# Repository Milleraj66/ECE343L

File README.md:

# ECE343L
MC68000 Eagle Schematic and Board

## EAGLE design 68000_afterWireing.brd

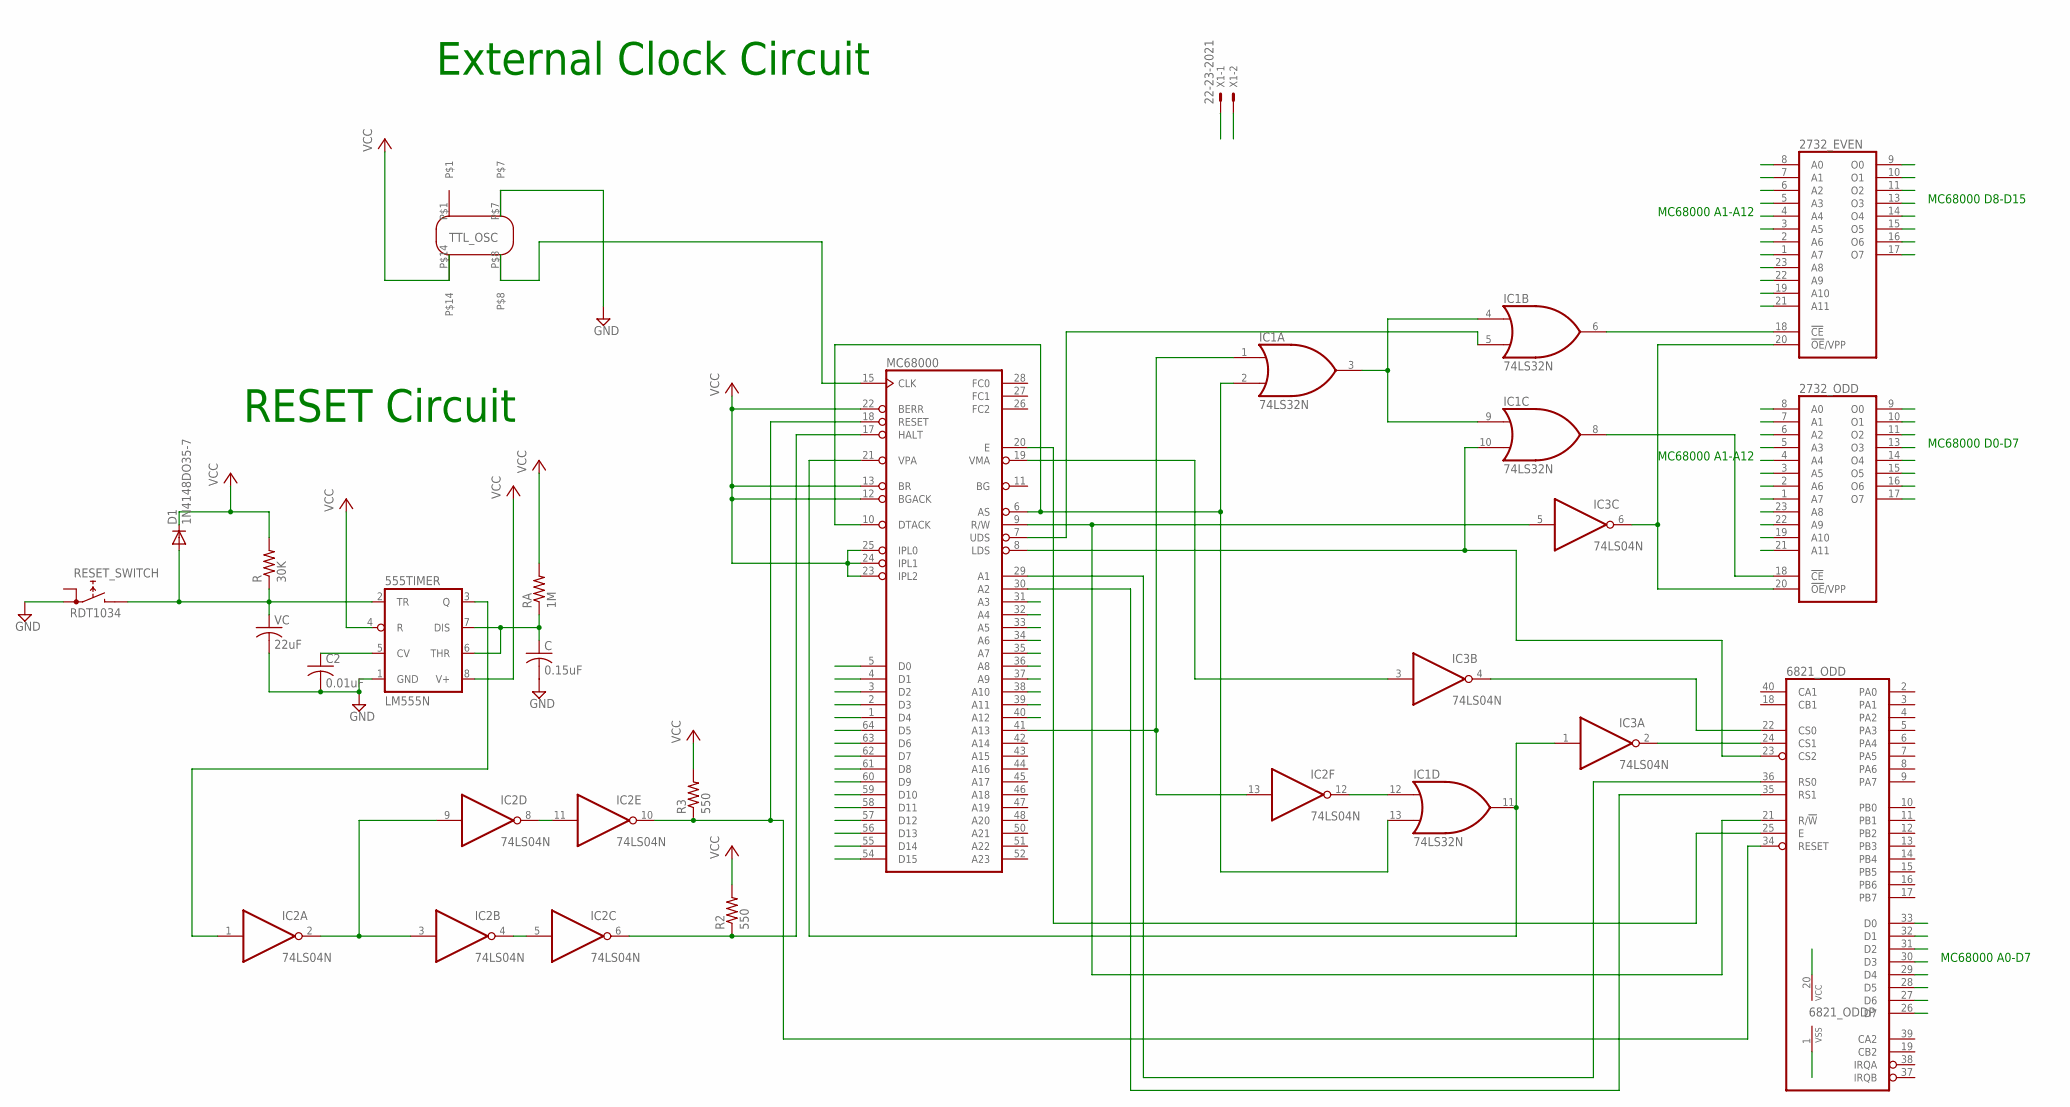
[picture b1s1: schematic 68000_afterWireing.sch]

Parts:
555TIMER: LM555N; DIL08
2732_EVEN, 2732_ODD: 2732; DIL24
6821_ODD: 6821; DIL40
C: 0.15uF; C025-024X044
C2: 0.01uF; C025-024X044
D1: 1N4148DO35-7; DO35-7
IC1: 74LS32N; DIL14
IC2, IC3: 74LS04N; DIL14
MC68000: MC68000P; DIL64
R: 30K; 0204V
R2, R3: 550; 0204V
RA: 1M; 0204V
RESET_SWITCH: RDT1034
U$1: TTL_OSCILLATOR
VC: 22uF; C025-024X044
X1: 22-23-2021

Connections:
A1: 2732_EVEN.8 (A0), 2732_ODD.8 (A0), 6821_ODD.36 (RS0), MC68000.29 (A1)
A2: 2732_EVEN.7 (A1), 2732_ODD.7 (A1), 6821_ODD.35 (RS1), MC68000.30 (A2)
A3: 2732_EVEN.6 (A2), 2732_ODD.6 (A2), MC68000.31 (A3)
A4: 2732_EVEN.5 (A3), 2732_ODD.5 (A3), MC68000.32 (A4)
A5: 2732_EVEN.4 (A4), 2732_ODD.4 (A4), MC68000.33 (A5)
A6: 2732_EVEN.3 (A5), 2732_ODD.3 (A5), MC68000.34 (A6)
A7: 2732_EVEN.2 (A6), 2732_ODD.2 (A6), MC68000.35 (A7)
A8: 2732_EVEN.1 (A7), 2732_ODD.1 (A7), MC68000.36 (A8)
A9: 2732_EVEN.23 (A8), 2732_ODD.23 (A8), MC68000.37 (A9)
A10: 2732_EVEN.22 (A9), 2732_ODD.22 (A9), MC68000.38 (A10)
A11: 2732_EVEN.19 (A10), 2732_ODD.19 (A10), MC68000.39 (A11)
A12: 2732_EVEN.21 (A11), 2732_ODD.21 (A11), MC68000.40 (A12)
D0: 2732_ODD.9 (O0), 6821_ODD.33 (D0), MC68000.5 (D0)
D1: 2732_ODD.10 (O1), 6821_ODD.32 (D1), MC68000.4 (D1)
D2: 2732_ODD.11 (O2), 6821_ODD.31 (D2), MC68000.3 (D2)
D3: 2732_ODD.13 (O3), 6821_ODD.30 (D3), MC68000.2 (D3)
D4: 2732_ODD.14 (O4), 6821_ODD.29 (D4), MC68000.1 (D4)
D5: 2732_ODD.15 (O5), 6821_ODD.28 (D5), MC68000.64 (D5)
D6: 2732_ODD.16 (O6), 6821_ODD.27 (D6), MC68000.63 (D6)
D7: 2732_ODD.17 (O7), 6821_ODD.26 (D7), MC68000.62 (D7)
D8: 2732_EVEN.9 (O0), MC68000.61 (D8)
D9: 2732_EVEN.10 (O1), MC68000.60 (D9)
D10: 2732_EVEN.11 (O2), MC68000.59 (D10)
D11: 2732_EVEN.13 (O3), MC68000.58 (D11)
D12: 2732_EVEN.14 (O4), MC68000.57 (D12)
D13: 2732_EVEN.15 (O5), MC68000.56 (D13)
D14: 2732_EVEN.16 (O6), MC68000.55 (D14)
D15: 2732_EVEN.17 (O7), MC68000.54 (D15)
GND: 555TIMER.1 (GND), 2732_EVEN.12 (GND), 2732_ODD.12 (GND), 6821_ODD.1 (VSS), C.2, C2.2, IC1.7 (GND), IC2.7 (GND), IC3.7 (GND), MC68000.16 (GND), MC68000.53 (GND), RESET_SWITCH.A1, U$1.P$7, VC.2, X1.2
unnamed: 6821_ODD.21 (R/!W), IC3.5 (I), MC68000.9 (R/W)
unnamed: 6821_ODD.24 (CS1), IC3.2 (O)
unnamed: IC1.1 (I0), IC2.13 (I), MC68000.41 (A13)
unnamed: IC1.3 (O), IC1.4 (I0), IC1.9 (I0)
unnamed: 2732_EVEN.20 (!OE!/VPP), 2732_ODD.20 (!OE!/VPP), IC3.6 (O)
unnamed: 6821_ODD.25 (E), MC68000.20 (E)
unnamed: IC1.5 (I1), MC68000.7 (UDS)
unnamed: 6821_ODD.23 (CS2), IC1.10 (I1), MC68000.8 (LDS)
unnamed: IC1.2 (I1), IC1.13 (I1), MC68000.6 (AS), MC68000.10 (DTACK)
unnamed: 6821_ODD.22 (CS0), IC3.4 (O)
unnamed: IC3.3 (I), MC68000.19 (VMA)
unnamed: IC1.12 (I0), IC2.12 (O)
unnamed: IC1.11 (O), IC3.1 (I), MC68000.21 (VPA)
unnamed: 555TIMER.5 (CV), C2.1
unnamed: 555TIMER.2 (TR), D1.A, R.1, RESET_SWITCH.B, VC.1
unnamed: 2732_EVEN.18 (!CE), IC1.6 (O)
unnamed: 555TIMER.6 (THR), 555TIMER.7 (DIS), C.1, RA.1
unnamed: 555TIMER.3 (Q), IC2.1 (I)
unnamed: IC2.4 (O), IC2.5 (I)
unnamed: IC2.6 (O), MC68000.17 (HALT), R2.1
unnamed: 6821_ODD.34 (RESET), IC2.10 (O), MC68000.18 (RESET), R3.1
unnamed: 2732_ODD.18 (!CE), IC1.8 (O)
unnamed: MC68000.15 (CLK), U$1.P$8
unnamed: IC2.2 (O), IC2.3 (I), IC2.9 (I)
unnamed: IC2.8 (O), IC2.11 (I)
VCC: 555TIMER.4 (R), 555TIMER.8 (V+), 2732_EVEN.24 (VCC), 2732_ODD.24 (VCC), 6821_ODD.20 (VCC), D1.C, IC1.14 (VCC), IC2.14 (VCC), IC3.14 (VCC), MC68000.12 (BGACK), MC68000.13 (BR), MC68000.14 (VCC), MC68000.22 (BERR), MC68000.23 (IPL2), MC68000.24 (IPL1), MC68000.25 (IPL0), MC68000.49 (VCC), R.2, R2.2, R3.2, RA.2, U$1.P$14, X1.1

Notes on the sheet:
RESET Circuit
External Clock Circuit
MC68000 D8-D15
MC68000 D0-D7
MC68000 A1-A12
MC68000 A0-D7

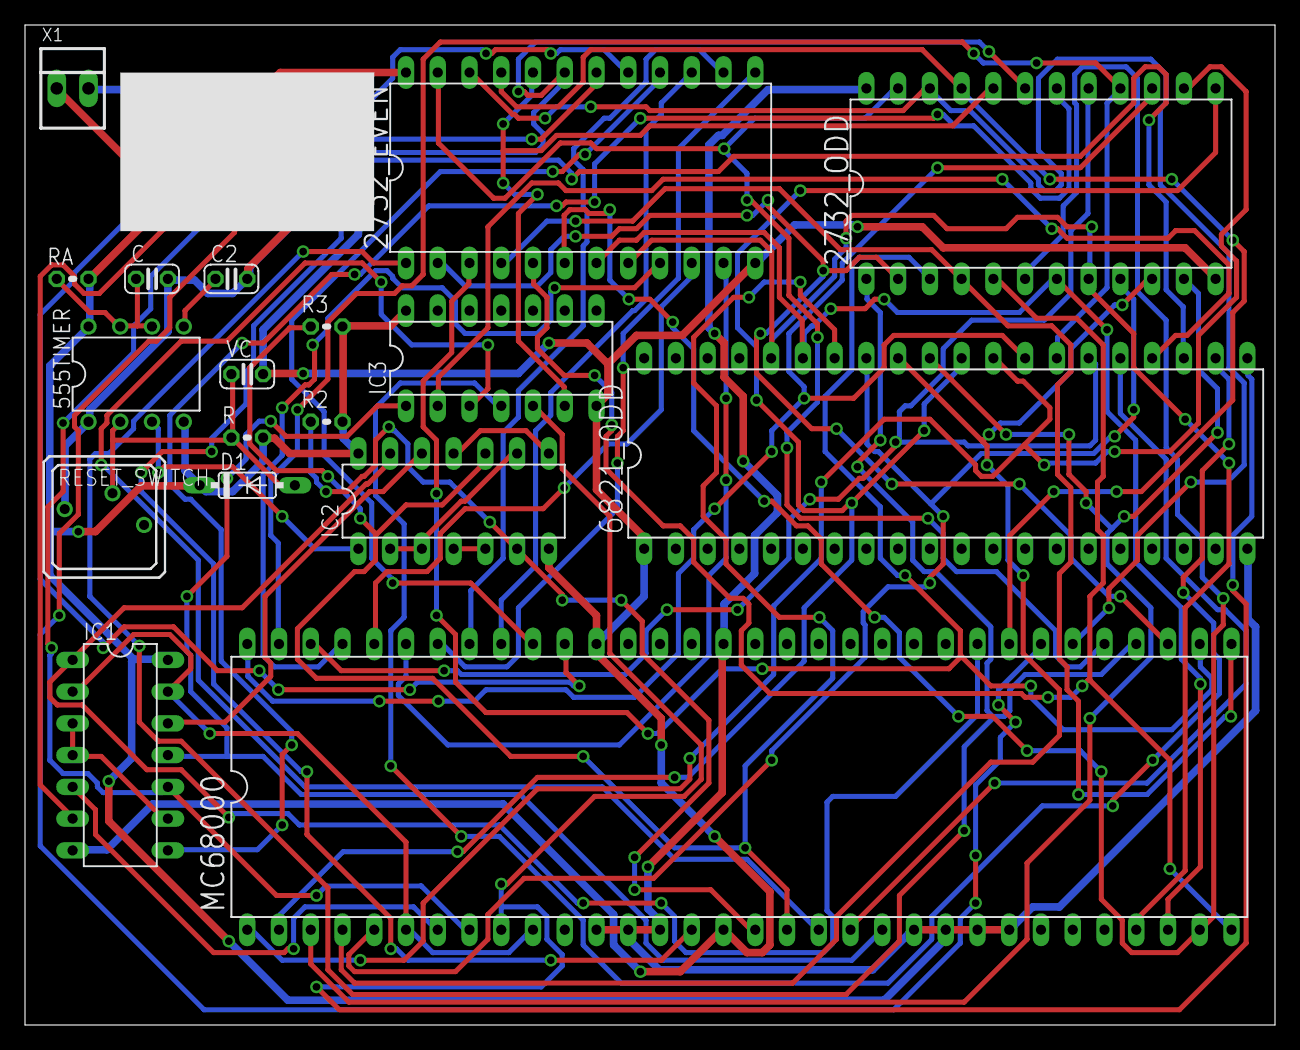
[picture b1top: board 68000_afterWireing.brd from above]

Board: 2 copper layers, 100.0 x 80.0 mm, 19 parts (0 on the bottom side), 55 nets.

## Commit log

2016-07-23 initial commit of schematic only
2016-07-23 added board
2016-07-24 Fixed errors and warnings after first autoroute. But Need to move components because their are still airwires after autorouting
2016-07-24 autoroute complete 100% and DRC passed
2016-07-25 Added gerber files
2016-07-26 added custom oscillator lbr, design is fully autorouted w/ gerber outputs
2016-07-29 FINAL: Sent to Bay Area Circuits
2016-08-03 added png
